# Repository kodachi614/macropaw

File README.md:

# MacroPaw Keypads

The MacroPaw keypads are a line of small yet fully-customizable mechanical
keyboards. (The name was originally from my son, years ago when he was young,
and the "paw" motif has kinda stuck.) The core of the MacroPaws is a Raspberry
Pi RP2040 with 16MiB of flash memory, a USB-C connector, and an attached key
matrix and RGB LEDs (which may or may not be under the keys). Some MacroPaws
have more capability than others; all are crazy customizable by writing Python
code. (Yes. Python. On a keyboard. It's insane and wonderful to live in the
future.)

|  |  |
| :-: | :-: |
| _Assembled KnGXT_     | _KnGXT PCB_ |

Currently extant MacroPaw boards include:

| Board ID | Description |
| :-: | :- |
| KnGXT | Mostly a proof-of-concept for an RP2040-based USB HID: it has 14 hotswappable MX keyswitches in a 3x5 layout like a number pad (including one 2U key, which is why it's 14 instead of 15), two rotary encoders with pushbuttons, and a bunch of RGB LEDs under the encoders and keys. |
| KnGYT | Mostly a proof-of-concept for double-sided assembly. It has ten hotswappable MX keyswitches in a 5x2 grid, ten RGB LEDs under the keys, and no rotary encoders. It's _much_ smaller than its sibling the KnGXT, because most of the electronics are on the back of the board. |
| Beatboxer KnH0F | A single-sided embedded keyboard controller for use in a [custom life-sized drum machine]. It has 8 RGB LEDs on the front of the board for hardware test and debugging, and its key matrix is an 8x8 grid that's mechanically arranged as a 16x4 grid of arcade buttons. |

[custom life-sized drum machine]: https://sig.gy/bbox/

Both the firmware and the hardware of the MacroPaws are **open source**.

## Firmware

The firmware is licensed under the GNU General Public License, version 3.0 or
later.

The `firmware` directory within each board's directory includes the firmware
source code firmware and the firmware license (in `firmware/LICENSE`).

The MacroPaw firmware is based on the [KMK Firmware], and on Adafruit's
[CircuitPython] and the [NeoPixelBackground] class. See
[BUILDING.md](BUILDING.md) for details about how to build the firmware,
including information about the versions of CircuitPython and KMK that are
used and how to get them.

Of course, if you don't want to build your own, you can just grab prebuilt
firmware for the [MacroPaw KnGXT], [MacroPaw KnGYT], and [MacroPaw Beatboxer
KnH0F] boards.

[KMK Firmware]: https://github.com/KMKfw/kmk_firmware/
[CircuitPython]: https://circuitpython.org/
[NeoPixelBackground]: https://learn.adafruit.com/intro-to-rp2040-pio-with-circuitpython/advanced-using-pio-to-drive-neopixels-in-the-background
[MacroPaw KnGXT]: https://www.kodachi.com/firmware/macropaw-KnGXT.uf2
[MacroPaw KnGYT]: https://www.kodachi.com/firmware/macropaw-KnGYT.uf2
[MacroPaw Beatboxer KnH0F]: https://www.kodachi.com/firmware/macropaw-Beatboxer.uf2

## Hardware

The hardware is licensed under the CERN Open Hardware License, version 2.0
or higher, Strongly Reciprocal.

The `hardware` directory within each board's directory includes the [KiCad] 7
design files for the hardware, the fabrication outputs used for the official
production runs of the hardware, and of course the hardware license (in
`hardware/LICENSE`).

[KiCad]: https://www.kicad.org/

## 3D Models

The `models` directory within some boards' directories includes the 3D models
for cases, etc., for the board. Boards without a `models` directory haven't
had models made yet!

The models are also licensed under the CERN Open Hardware License, version 2.0
or higher, Strongly Reciprocal.

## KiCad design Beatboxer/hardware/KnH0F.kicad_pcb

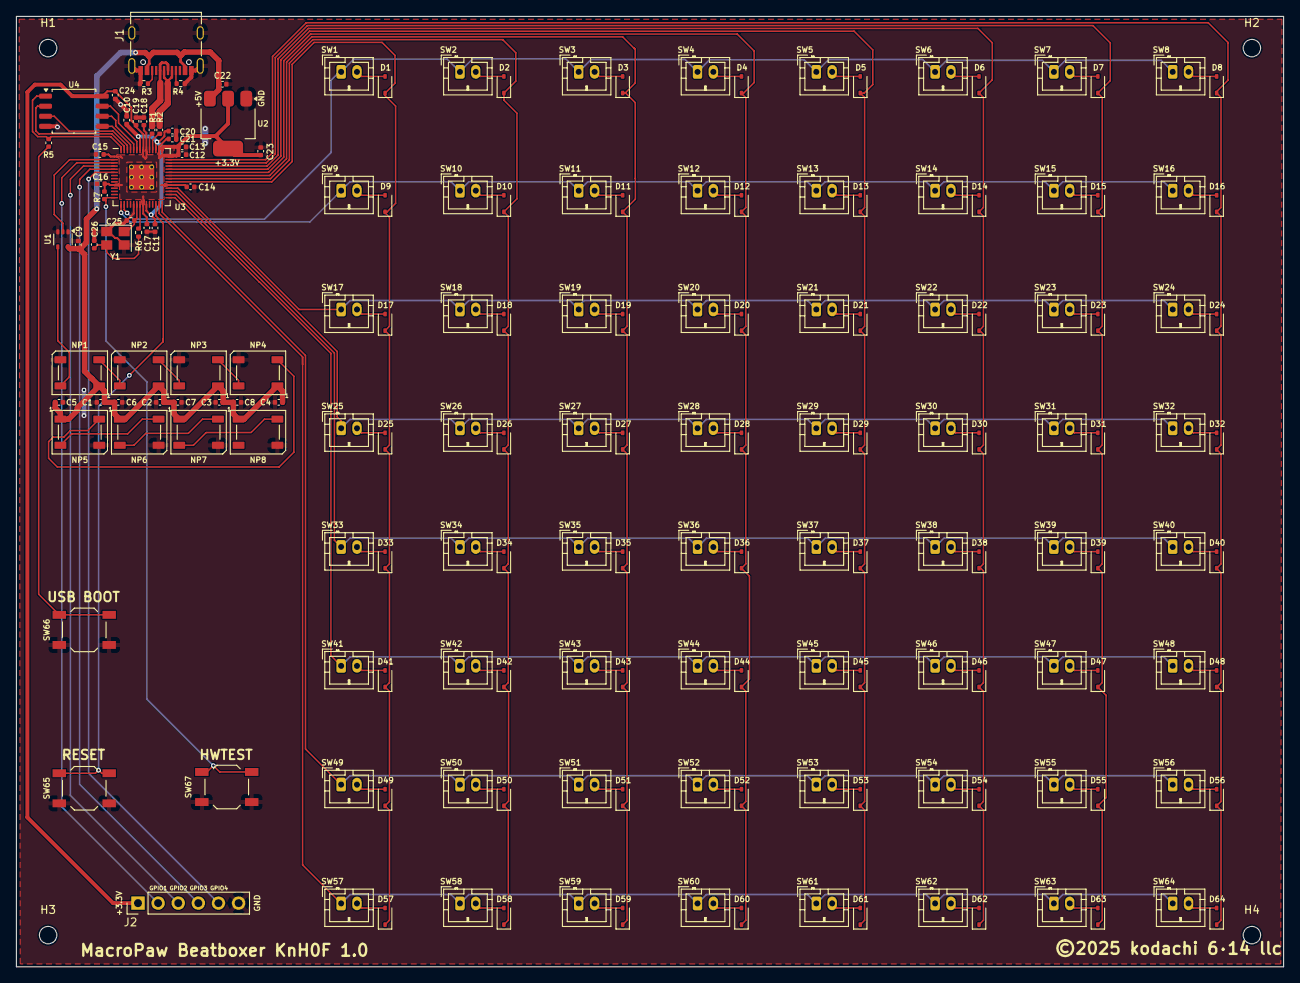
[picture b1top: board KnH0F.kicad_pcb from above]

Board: 2 copper layers, 160.0 x 120.0 mm, 183 parts (0 on the bottom side), 115 nets.

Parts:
C1, C2, C3, C4, C5, C6, C7, C8, C9, C22, C23, C24: 10uF; C_0402_1005Metric
C10, C11, C12, C13, C14, C15, C16, C17, C18, C19: 100nF; C_0402_1005Metric
C20, C21: 1uF; C_0402_1005Metric
C25, C26: 30pF; C_0402_1005Metric
D1, D2, D3, D4, D5, D6, D7, D8, D9, D10, D11, D12, D13, D14, D15, D16, D17, D18, D19, D20, D21, D22, D23, D24, D25, D26, D27, D28, D29, D30, D31, D32, D33, D34, D35, D36, D37, D38, D39, D40, D41, D42, D43, D44, D45, D46, D47, D48, D49, D50, D51, D52, D53, D54, D55, D56, D57, D58, D59, D60, D61, D62, D63, D64: 1N4148; D_SOD-323
H1, H2, H3, H4: MountingHole; MountingHole_2.2mm_M2
J1: USB_C_Receptacle_USB2.0_16P; USB_C_Receptacle_Palconn_UTC16-G
J2: Conn_01x06_Pin; PinHeader_1x06_P2.54mm_Vertical
NP1, NP2, NP3, NP4, NP5, NP6, NP7, NP8: WS2812B; LED_WS2812B_PLCC4_5.0x5.0mm_P3.2mm
R1, R2: 27; C_0402_1005Metric
R3, R4: 5.1k; R_0402_1005Metric
R5, R7: 1k; C_0402_1005Metric
R6: 1k; R_0402_1005Metric
SW1, SW2, SW3, SW4, SW5, SW6, SW7, SW8, SW9, SW10, SW11, SW12, SW13, SW14, SW15, SW16, SW17, SW18, SW19, SW20, SW21, SW22, SW23, SW24, SW25, SW26, SW27, SW28, SW29, SW30, SW31, SW32, SW33, SW34, SW35, SW36, SW37, SW38, SW39, SW40, SW41, SW42, SW43, SW44, SW45, SW46, SW47, SW48, SW49, SW50, SW51, SW52, SW53, SW54, SW55, SW56, SW57, SW58, SW59, SW60, SW61, SW62, SW63, SW64: SW_Push_45deg; JST_PH_B2B-PH-K_1x02_P2.00mm_Vertical
SW65, SW66, SW67: SW_Push; SW_SPST_TL3342
U1: 74AHC1G125; SOT-353_SC-70-5
U2: AMS1117-3.3; SOT-223-3_TabPin2
U3: RP2040; RP2040-QFN-56
U4: W25Q128JVS; SOIC-8_5.3x5.3mm_P1.27mm
Y1: 12MHz; Crystal_SMD_3225-4Pin_3.2x2.5mm

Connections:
+1V1: C10.1, C11.1, C20.1, U3.23 (DVDD), U3.45 (VREG_VOUT), U3.50 (DVDD)
+3V3: C12.1, C13.1, C14.1, C15.1, C16.1, C17.1, C18.1, C19.1, C21.1, C23.1, C24.1, J2.1, R7.1, U2.2 (VO), U3.1 (IOVDD), U3.10 (IOVDD), U3.22 (IOVDD), U3.33 (IOVDD), U3.42 (IOVDD), U3.43 (ADC_AVDD), U3.44 (VREG_IN), U3.48 (USB_VDD), U3.49 (IOVDD), U4.8 (VCC)
+5V: C1.1, C2.1, C3.1, C4.1, C5.1, C6.1, C7.1, C8.1, C9.1, C22.1, J1.A4 (VBUS), J1.A9 (VBUS), J1.B4 (VBUS), J1.B9 (VBUS), NP1.1 (VDD), NP2.1 (VDD), NP3.1 (VDD), NP4.1 (VDD), NP5.1 (VDD), NP6.1 (VDD), NP7.1 (VDD), NP8.1 (VDD), U1.5 (VCC), U2.3 (VI)
/GPIO1: J2.2, U3.3 (GPIO1)
/GPIO2: J2.3, U3.4 (GPIO2)
/GPIO3: J2.4, U3.5 (GPIO3)
/GPIO4: J2.5, U3.6 (GPIO4)
/HWTEST: R7.2, SW67.1, U3.14 (GPIO11)
/NEO3V3: U1.2, U3.2 (GPIO0)
/NEOPXL: NP1.4 (DIN), U1.4
/QSPI_SCLK: U3.52 (QSPI_SCLK), U4.6 (CLK)
/QSPI_SD0: U3.53 (QSPI_SD0), U4.5 (DI/IO_{0})
/QSPI_SD1: U3.55 (QSPI_SD1), U4.2 (DO/IO_{1})
/QSPI_SD2: U3.54 (QSPI_SD2), U4.3 (~WP/IO_{2})
/QSPI_SD3: U3.51 (QSPI_SD3), U4.7 (~HOLD/~RESET/IO_{3})
/QSPI_SS: R5.1, U3.56 (QSPI_SS), U4.1 (~CS)
/RUN: SW65.2, U3.26 (RUN)
/USB_CC1: J1.A5 (CC1), R4.2
/USB_CC2: J1.B5 (CC2), R3.2
/USB_D+: J1.A6 (D+), J1.B6 (D+), R1.1
/USB_D-: J1.A7 (D-), J1.B7 (D-), R2.1
/XIN: C25.1, U3.20 (XIN), Y1.1
/XOUT: R6.1, U3.21 (XOUT)
/~USB_BOOT: R5.2, SW66.2
COL0: D1.1 (K), D9.1 (K), D17.1 (K), D25.1 (K), D33.1 (K), D41.1 (K), D49.1 (K), D57.1 (K), U3.34 (GPIO22)
COL1: D2.1 (K), D10.1 (K), D18.1 (K), D26.1 (K), D34.1 (K), D42.1 (K), D50.1 (K), D58.1 (K), U3.35 (GPIO23)
COL2: D3.1 (K), D11.1 (K), D19.1 (K), D27.1 (K), D35.1 (K), D43.1 (K), D51.1 (K), D59.1 (K), U3.36 (GPIO24)
COL3: D4.1 (K), D12.1 (K), D20.1 (K), D28.1 (K), D36.1 (K), D44.1 (K), D52.1 (K), D60.1 (K), U3.37 (GPIO25)
COL4: D5.1 (K), D13.1 (K), D21.1 (K), D29.1 (K), D37.1 (K), D45.1 (K), D53.1 (K), D61.1 (K), U3.38 (GPIO26_ADC0)
COL5: D6.1 (K), D14.1 (K), D22.1 (K), D30.1 (K), D38.1 (K), D46.1 (K), D54.1 (K), D62.1 (K), U3.39 (GPIO27_ADC1)
COL6: D7.1 (K), D15.1 (K), D23.1 (K), D31.1 (K), D39.1 (K), D47.1 (K), D55.1 (K), D63.1 (K), U3.40 (GPIO28_ADC2)
COL7: D8.1 (K), D16.1 (K), D24.1 (K), D32.1 (K), D40.1 (K), D48.1 (K), D56.1 (K), D64.1 (K), U3.41 (GPIO29_ADC3)
GND: C1.2, C2.2, C3.2, C4.2, C5.2, C6.2, C7.2, C8.2, C9.2, C10.2, C11.2, C12.2, C13.2, C14.2, C15.2, C16.2, C17.2, C18.2, C19.2, C20.2, C21.2, C22.2, C23.2, C24.2, C25.2, C26.2, J1.A1 (GND), J1.A12 (GND), J1.B1 (GND), J1.B12 (GND), J1.S1 (SHIELD), J2.6, NP1.3 (VSS), NP2.3 (VSS), NP3.3 (VSS), NP4.3 (VSS), NP5.3 (VSS), NP6.3 (VSS), NP7.3 (VSS), NP8.3 (VSS), R3.1, R4.1, SW65.1, SW66.1, SW67.2, U1.1, U1.3 (GND), U2.1 (GND), U3.19 (TESTEN), U3.57 (GND), U4.4 (GND), Y1.2, Y1.4
unnamed: C26.1, R6.2, Y1.3
unnamed: D1.2 (A), SW1.2
unnamed: D2.2 (A), SW2.2
unnamed: D3.2 (A), SW3.2
unnamed: D4.2 (A), SW4.2
unnamed: D5.2 (A), SW5.2
unnamed: D6.2 (A), SW6.2
unnamed: D7.2 (A), SW7.2
unnamed: D8.2 (A), SW8.2
unnamed: D9.2 (A), SW9.2
unnamed: D10.2 (A), SW10.2
unnamed: D11.2 (A), SW11.2
unnamed: D12.2 (A), SW12.2
unnamed: D13.2 (A), SW13.2
unnamed: D14.2 (A), SW14.2
unnamed: D15.2 (A), SW15.2
unnamed: D16.2 (A), SW16.2
unnamed: D17.2 (A), SW17.2
unnamed: D18.2 (A), SW18.2
unnamed: D19.2 (A), SW19.2
unnamed: D20.2 (A), SW20.2
unnamed: D21.2 (A), SW21.2
unnamed: D22.2 (A), SW22.2
unnamed: D23.2 (A), SW23.2
unnamed: D24.2 (A), SW24.2
unnamed: D25.2 (A), SW25.2
unnamed: D26.2 (A), SW26.2
unnamed: D27.2 (A), SW27.2
unnamed: D28.2 (A), SW28.2
unnamed: D29.2 (A), SW29.2
unnamed: D30.2 (A), SW30.2
unnamed: D31.2 (A), SW31.2
unnamed: D32.2 (A), SW32.2
unnamed: D33.2 (A), SW33.2
unnamed: D34.2 (A), SW34.2
unnamed: D35.2 (A), SW35.2
unnamed: D36.2 (A), SW36.2
unnamed: D37.2 (A), SW37.2
unnamed: D38.2 (A), SW38.2
unnamed: D39.2 (A), SW39.2
unnamed: D40.2 (A), SW40.2
unnamed: D41.2 (A), SW41.2
unnamed: D42.2 (A), SW42.2
unnamed: D43.2 (A), SW43.2
unnamed: D44.2 (A), SW44.2
unnamed: D45.2 (A), SW45.2
unnamed: D46.2 (A), SW46.2
unnamed: D47.2 (A), SW47.2
unnamed: D48.2 (A), SW48.2
unnamed: D49.2 (A), SW49.2
unnamed: D50.2 (A), SW50.2
unnamed: D51.2 (A), SW51.2
unnamed: D52.2 (A), SW52.2
unnamed: D53.2 (A), SW53.2
unnamed: D54.2 (A), SW54.2
unnamed: D55.2 (A), SW55.2
unnamed: D56.2 (A), SW56.2
unnamed: D57.2 (A), SW57.2
unnamed: D58.2 (A), SW58.2
unnamed: D59.2 (A), SW59.2
unnamed: D60.2 (A), SW60.2
unnamed: D61.2 (A), SW61.2
unnamed: D62.2 (A), SW62.2
unnamed: D63.2 (A), SW63.2
unnamed: D64.2 (A), SW64.2
unnamed: NP1.2 (DOUT), NP2.4 (DIN)
unnamed: NP2.2 (DOUT), NP3.4 (DIN)
unnamed: NP3.2 (DOUT), NP4.4 (DIN)
unnamed: NP4.2 (DOUT), NP5.4 (DIN)
unnamed: NP5.2 (DOUT), NP6.4 (DIN)
unnamed: NP6.2 (DOUT), NP7.4 (DIN)
unnamed: NP7.2 (DOUT), NP8.4 (DIN)
unnamed: R2.2, U3.46 (USB_DM)
unnamed: R1.2, U3.47 (USB_DP)
ROW0: SW1.1, SW2.1, SW3.1, SW4.1, SW5.1, SW6.1, SW7.1, SW8.1, U3.16 (GPIO13)
ROW1: SW9.1, SW10.1, SW11.1, SW12.1, SW13.1, SW14.1, SW15.1, SW16.1, U3.15 (GPIO12)
ROW2: SW17.1, SW18.1, SW19.1, SW20.1, SW21.1, SW22.1, SW23.1, SW24.1, U3.32 (GPIO21)
ROW3: SW25.1, SW26.1, SW27.1, SW28.1, SW29.1, SW30.1, SW31.1, SW32.1, U3.31 (GPIO20)
ROW4: SW33.1, SW34.1, SW35.1, SW36.1, SW37.1, SW38.1, SW39.1, SW40.1, U3.30 (GPIO19)
ROW5: SW41.1, SW42.1, SW43.1, SW44.1, SW45.1, SW46.1, SW47.1, SW48.1, U3.29 (GPIO18)
ROW6: SW49.1, SW50.1, SW51.1, SW52.1, SW53.1, SW54.1, SW55.1, SW56.1, U3.28 (GPIO17)
ROW7: SW57.1, SW58.1, SW59.1, SW60.1, SW61.1, SW62.1, SW63.1, SW64.1, U3.27 (GPIO16)

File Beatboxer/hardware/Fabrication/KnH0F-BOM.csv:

Comment,Designator,Footprint,LCSC Part Number
10uF,"C1,C2,C3,C4,C5,C6,C7,C8,C9,C22,C23,C24",0402,C15525
100nF,"C10,C11,C12,C13,C14,C15,C16,C17,C18,C19",0402,C1525
1uF,"C20,C21",0402,C52923
30pF,"C25,C26",0402,C1570
1N4148,"D1,D2,D3,D4,D5,D6,D7,D8,D9,D10,D11,D12,D13,D14,D15,D16,D17,D18,D19,D20,D21,D22,D23,D24,D25,D26,D27,D28,D29,D30,D31,D32,D33,D34,D35,D36,D37,D38,D39,D40,D41,D42,D43,D44,D45,D46,D47,D48,D49,D50,D51,D52,D53,D54,D55,D56,D57,D58,D59,D60,D61,D62,D63,D64",SOD-323,C2128
USB_C_Receptacle_USB2.0_16P,J1,USB_C_Receptacle_Palconn_UTC16-G,C165948
WS2812B,"NP1,NP2,NP3,NP4,NP5,NP6,NP7,NP8",PLCC4 5.0x5.0mm,C2761795
27,"R1,R2",0402,C25100
5.1k,"R3,R4",0402,C25905
1k,"R5,R7",0402,C11702
1k,R6,0402,C11702
SW_Push_45deg,"SW1,SW2,SW3,SW4,SW5,SW6,SW7,SW8,SW9,SW10,SW11,SW12,SW13,SW14,SW15,SW16,SW17,SW18,SW19,SW20,SW21,SW22,SW23,SW24,SW25,SW26,SW27,SW28,SW29,SW30,SW31,SW32,SW33,SW34,SW35,SW36,SW37,SW38,SW39,SW40,SW41,SW42,SW43,SW44,SW45,SW46,SW47,SW48,SW49,SW50,SW51,SW52,SW53,SW54,SW55,SW56,SW57,SW58,SW59,SW60,SW61,SW62,SW63,SW64",JST PH B2B-PH-K 1x02 P2.00mm Vertical,C131337
SW_Push,"SW65,SW66,SW67",SPST_TL3342,C318884
74AHC1G125,U1,SOT-353,C151417
AMS1117-3.3,U2,SOT-223,C6186
RP2040,U3,QFN-56,C2040
W25Q128JVS,U4,SOIC-8 5.3x5.3mm P1.27mm,C97521
12MHz,Y1,SMD_3225,C9002

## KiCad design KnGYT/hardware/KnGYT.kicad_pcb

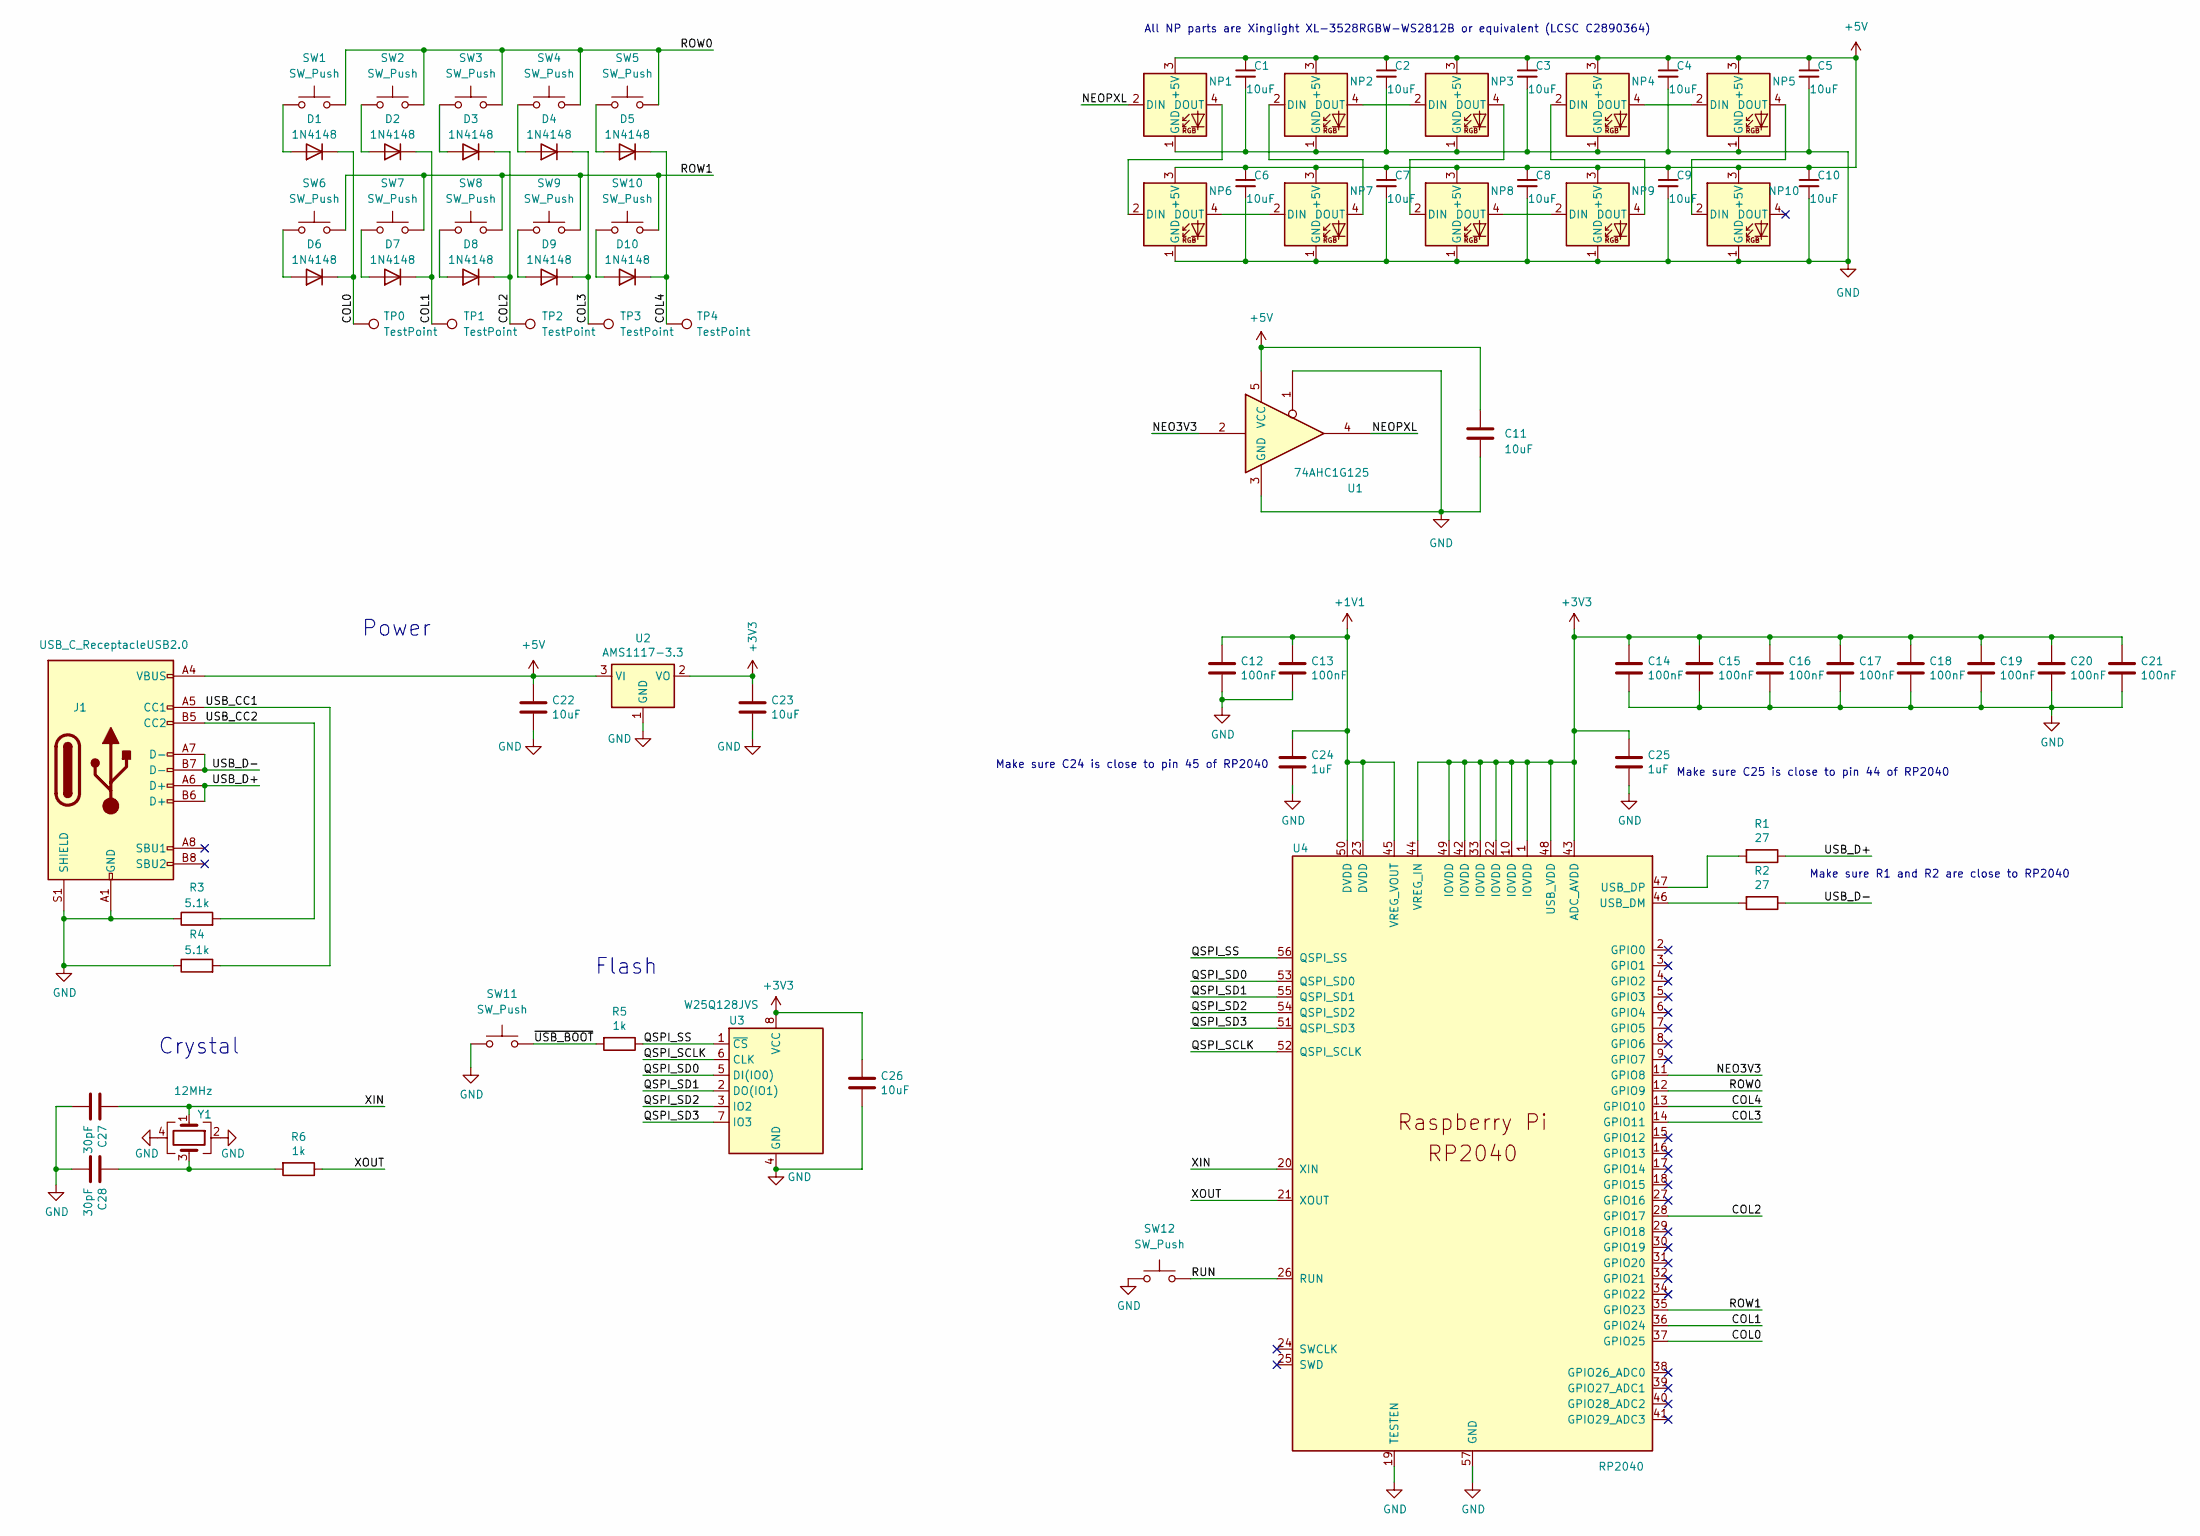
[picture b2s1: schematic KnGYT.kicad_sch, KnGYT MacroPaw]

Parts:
C1, C2, C3, C4, C5, C6, C7, C8, C9, C10, C11, C22, C23, C26: 10uF; C_0402_1005Metric; LCSC C15525
C12, C13, C14, C15, C16, C17, C18, C19, C20, C21: 100nF; C_0402_1005Metric; LCSC C1525
C24, C25: 1uF; C_0402_1005Metric; LCSC C52923
C27, C28: 30pF; C_0402_1005Metric; LCSC C1570
D1, D2, D3, D4, D5, D6, D7, D8, D9, D10: 1N4148; D_SOD-323F; LCSC C2128
J1: USB_C_ReceptacleUSB2.0; USB_C_Receptacle_Palconn_UTC16-G; LCSC C165948
NP1, NP2, NP3, NP4, NP5, NP6, NP7, NP8, NP9, NP10: WS2812B; LED XL-3528RGBW-WS2812B (3.5x2.8, C2890364); LCSC C2890364
R1, R2: 27; C_0402_1005Metric; LCSC C25100
R3, R4: 5.1k; R_0402_1005Metric; LCSC C25905
R5: 1k; C_0402_1005Metric; LCSC C11702
R6: 1k; R_0402_1005Metric; LCSC C11702
SW1, SW2, SW3, SW4, SW5, SW6, SW7, SW8, SW9, SW10: SW_Push; Flipped_Hotswap_Kailh_MX_1.00u (C5184526); LCSC C5184526
SW11, SW12: SW_Push; SW_SPST_TL3342; LCSC C318884
TP0, TP1, TP2, TP3, TP4: TestPoint; TestPoint_Pad_1.5x1.5mm
U1: 74AHC1G125; SOT-353_SC-70-5; LCSC C151417
U2: AMS1117-3.3; SOT-223-3_TabPin2; LCSC C6186
U3: W25Q128JVS; SOIC-8_5.23x5.23mm_P1.27mm; LCSC C97521
U4: RP2040; RP2040-QFN-56; LCSC C2040
Y1: 12MHz; Crystal_SMD_3225-4Pin_3.2x2.5mm; LCSC C9002

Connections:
+1V1: C12.1, C13.1, C24.1, U4.23 (DVDD), U4.45 (VREG_VOUT), U4.50 (DVDD)
+3V3: C14.1, C15.1, C16.1, C17.1, C18.1, C19.1, C20.1, C21.1, C23.1, C25.1, C26.1, U2.2 (VO), U3.8 (VCC), U4.1 (IOVDD), U4.10 (IOVDD), U4.22 (IOVDD), U4.33 (IOVDD), U4.42 (IOVDD), U4.43 (ADC_AVDD), U4.44 (VREG_IN), U4.48 (USB_VDD), U4.49 (IOVDD)
+5V: C1.1, C2.1, C3.1, C4.1, C5.1, C6.1, C7.1, C8.1, C9.1, C10.1, C11.1, C22.1, J1.A4 (VBUS), J1.A9 (VBUS), J1.B4 (VBUS), J1.B9 (VBUS), NP1.3 (+5V), NP2.3 (+5V), NP3.3 (+5V), NP4.3 (+5V), NP5.3 (+5V), NP6.3 (+5V), NP7.3 (+5V), NP8.3 (+5V), NP9.3 (+5V), NP10.3 (+5V), U1.5 (VCC), U2.3 (VI)
/COL0: D1.1 (K), D6.1 (K), TP0.1, U4.37 (GPIO25)
/COL1: D2.1 (K), D7.1 (K), TP1.1, U4.36 (GPIO24)
/COL2: D3.1 (K), D8.1 (K), TP2.1, U4.28 (GPIO17)
/COL3: D4.1 (K), D9.1 (K), TP3.1, U4.14 (GPIO11)
/COL4: D5.1 (K), D10.1 (K), TP4.1, U4.13 (GPIO10)
/NEO3V3: U1.2, U4.11 (GPIO8)
/NEOPXL: NP1.2 (DIN), U1.4
/QSPI_SCLK: U3.6 (CLK), U4.52 (QSPI_SCLK)
/QSPI_SD0: U3.5 (DI(IO0)), U4.53 (QSPI_SD0)
/QSPI_SD1: U3.2 (DO(IO1)), U4.55 (QSPI_SD1)
/QSPI_SD2: U3.3 (IO2), U4.54 (QSPI_SD2)
/QSPI_SD3: U3.7 (IO3), U4.51 (QSPI_SD3)
/QSPI_SS: R5.1, U3.1 (~CS), U4.56 (QSPI_SS)
/ROW0: SW1.2, SW2.2, SW3.2, SW4.2, SW5.2, U4.12 (GPIO9)
/ROW1: SW6.2, SW7.2, SW8.2, SW9.2, SW10.2, U4.35 (GPIO23)
/RUN: SW12.2, U4.26 (RUN)
/USB_CC1: J1.A5 (CC1), R4.2
/USB_CC2: J1.B5 (CC2), R3.2
/USB_D+: J1.A6 (D+), J1.B6 (D+), R1.1
/USB_D-: J1.A7 (D-), J1.B7 (D-), R2.1
/XIN: C27.1, U4.20 (XIN), Y1.1
/XOUT: R6.1, U4.21 (XOUT)
/~USB_BOOT: R5.2, SW11.2
GND: C1.2, C2.2, C3.2, C4.2, C5.2, C6.2, C7.2, C8.2, C9.2, C10.2, C11.2, C12.2, C13.2, C14.2, C15.2, C16.2, C17.2, C18.2, C19.2, C20.2, C21.2, C22.2, C23.2, C24.2, C25.2, C26.2, C27.2, C28.2, J1.A1 (GND), J1.A12 (GND), J1.B1 (GND), J1.B12 (GND), J1.S1 (SHIELD), NP1.1 (GND), NP2.1 (GND), NP3.1 (GND), NP4.1 (GND), NP5.1 (GND), NP6.1 (GND), NP7.1 (GND), NP8.1 (GND), NP9.1 (GND), NP10.1 (GND), R3.1, R4.1, SW11.1, SW12.1, U1.1, U1.3 (GND), U2.1 (GND), U3.4 (GND), U4.19 (TESTEN), U4.57 (GND), Y1.2, Y1.4
unnamed: C28.1, R6.2, Y1.3
unnamed: D1.2 (A), SW1.1
unnamed: D2.2 (A), SW2.1
unnamed: D3.2 (A), SW3.1
unnamed: D4.2 (A), SW4.1
unnamed: D5.2 (A), SW5.1
unnamed: D6.2 (A), SW6.1
unnamed: D7.2 (A), SW7.1
unnamed: D8.2 (A), SW8.1
unnamed: D9.2 (A), SW9.1
unnamed: D10.2 (A), SW10.1
unnamed: NP1.4 (DOUT), NP6.2 (DIN)
unnamed: NP2.2 (DIN), NP7.4 (DOUT)
unnamed: NP2.4 (DOUT), NP3.2 (DIN)
unnamed: NP3.4 (DOUT), NP8.2 (DIN)
unnamed: NP4.2 (DIN), NP9.4 (DOUT)
unnamed: NP4.4 (DOUT), NP5.2 (DIN)
unnamed: NP6.4 (DOUT), NP7.2 (DIN)
unnamed: NP8.4 (DOUT), NP9.2 (DIN)
unnamed: NP5.4 (DOUT), NP10.2 (DIN)
unnamed: R2.2, U4.46 (USB_DM)
unnamed: R1.2, U4.47 (USB_DP)

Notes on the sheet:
Crystal
Make sure R1 and R2 are close to RP2040
Make sure C25 is close to pin 44 of RP2040
All NP parts are Xinglight XL-3528RGBW-WS2812B or equivalent (LCSC C2890364)
Make sure C24 is close to pin 45 of RP2040
Flash
Power

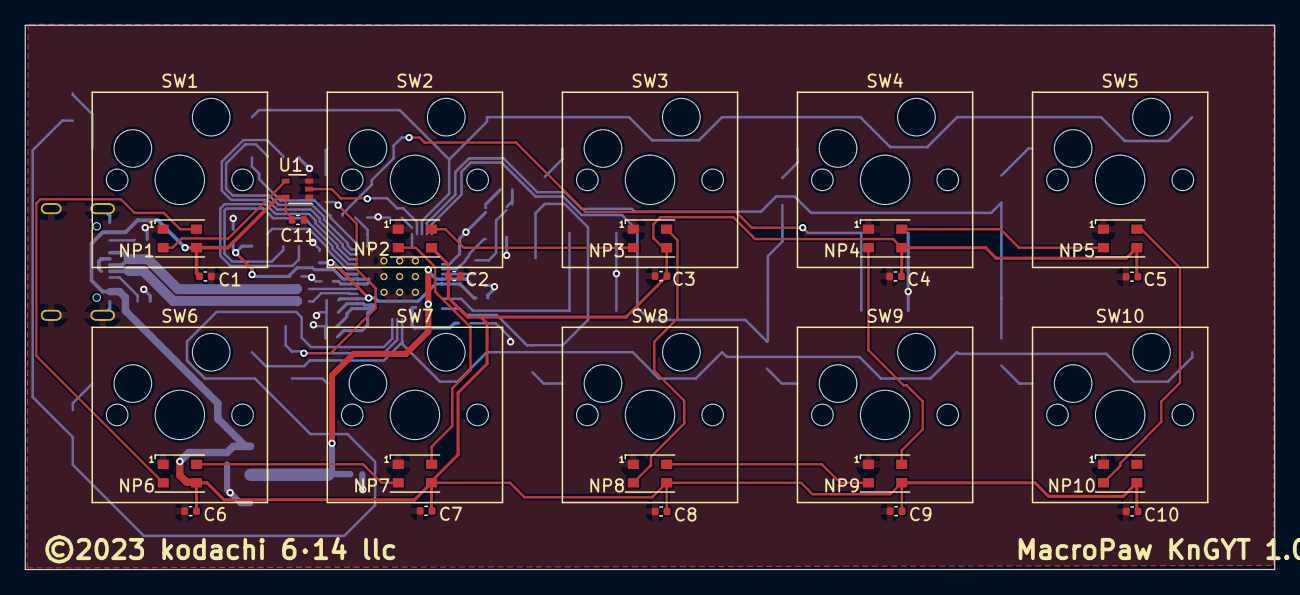
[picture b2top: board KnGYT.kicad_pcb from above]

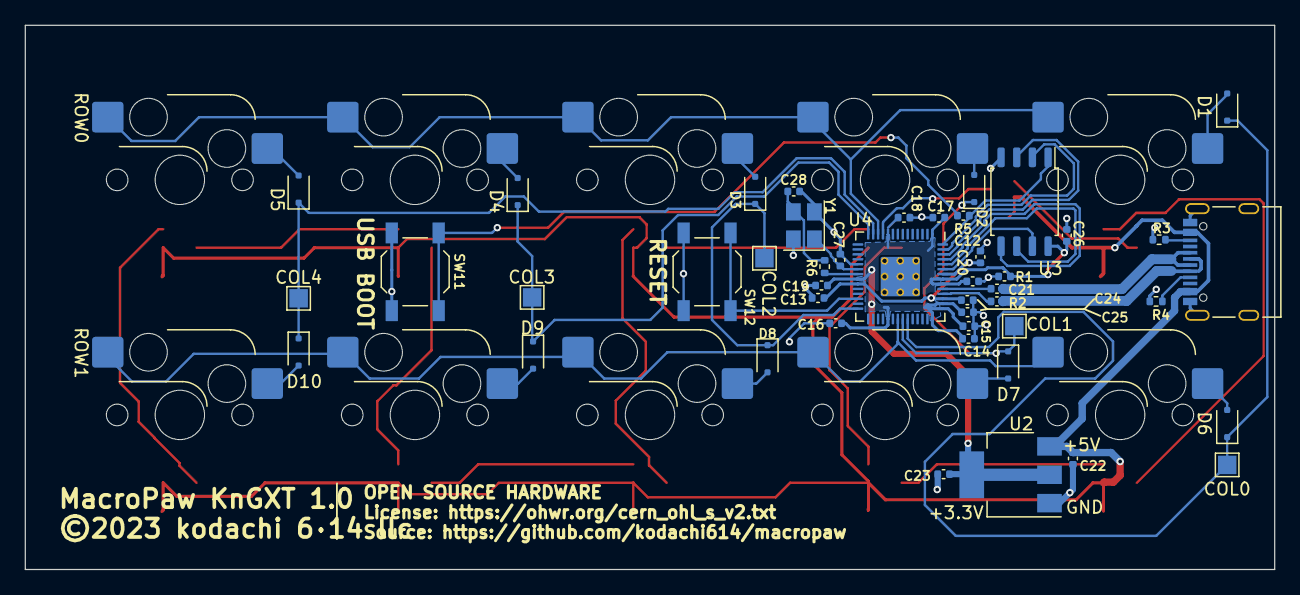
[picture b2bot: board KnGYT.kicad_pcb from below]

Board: 2 copper layers, 101.2 x 44.1 mm, 77 parts (55 on the bottom side), 49 nets.

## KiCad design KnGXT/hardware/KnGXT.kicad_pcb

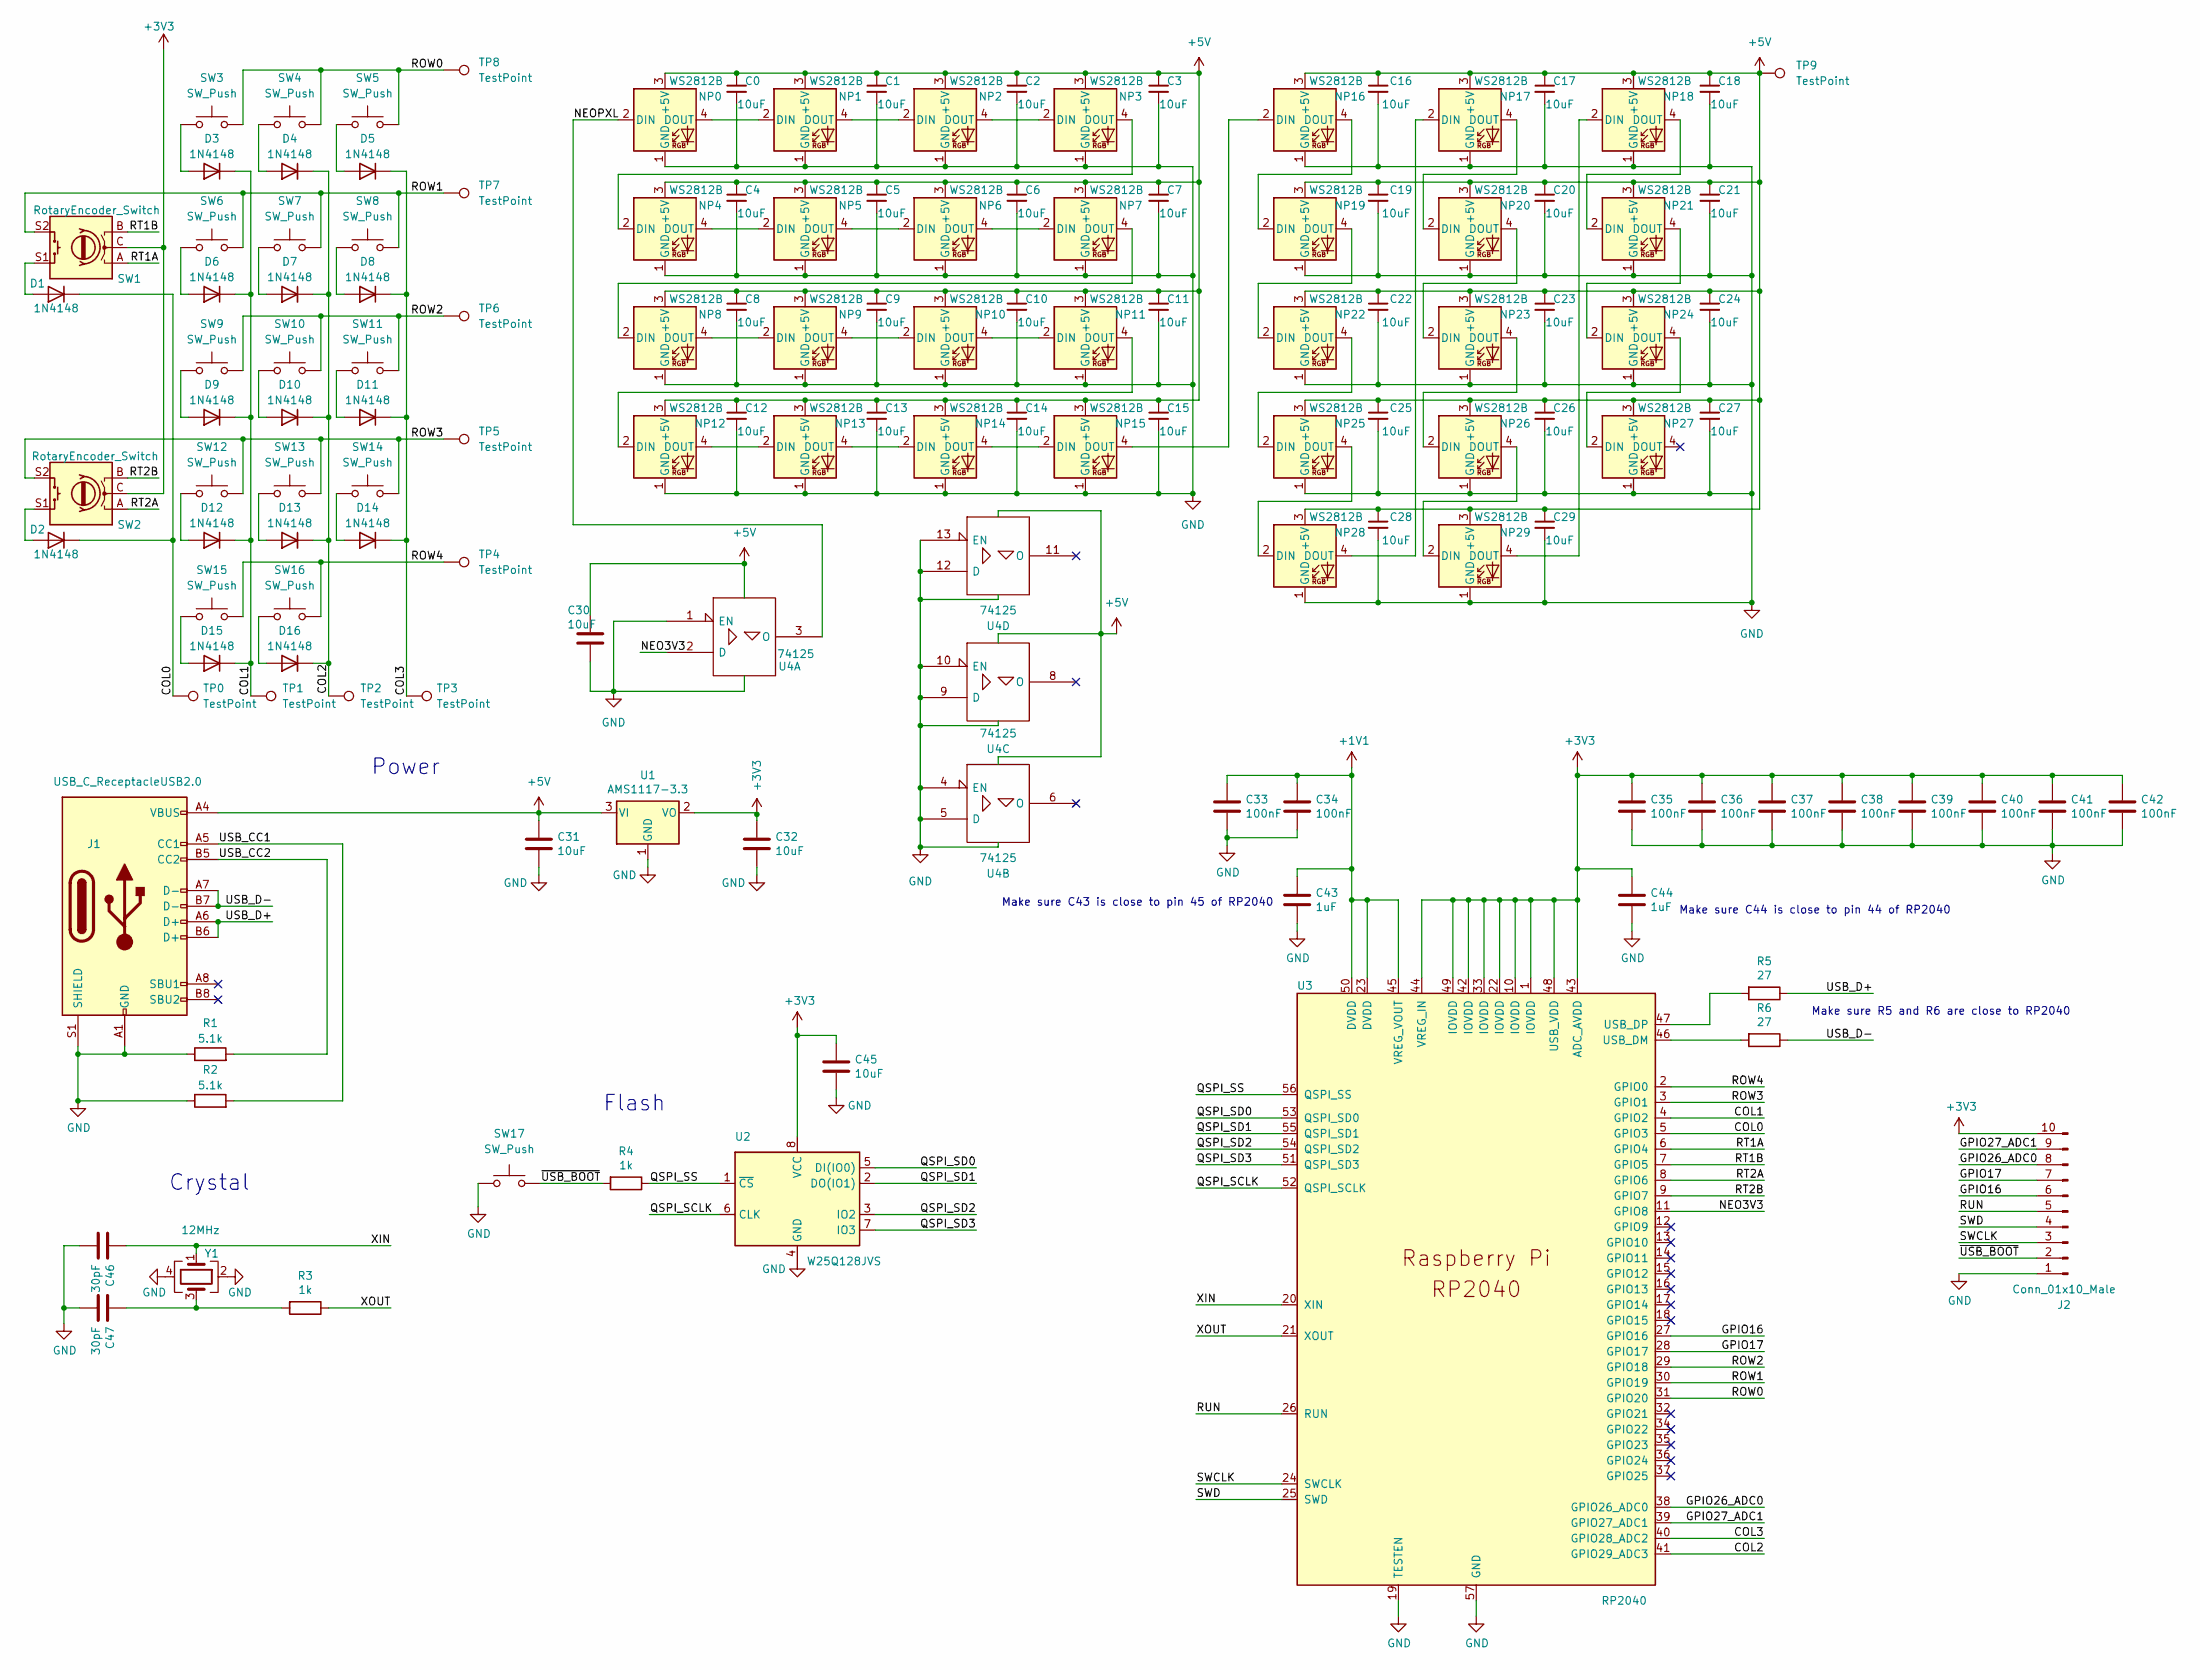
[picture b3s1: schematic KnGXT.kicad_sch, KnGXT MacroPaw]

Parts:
C0, C1, C2, C3, C4, C5, C6, C7, C8, C9, C10, C11, C12, C13, C14, C15, C16, C17, C18, C19, C20, C21, C22, C23, C24, C25, C26, C27, C28, C29, C30, C31, C32, C45: 10uF; C_0402_1005Metric; LCSC C15525
C33, C34, C35, C36, C37, C38, C39, C40, C41, C42: 100nF; C_0402_1005Metric; LCSC C1525
C43, C44: 1uF; C_0402_1005Metric; LCSC C52923
C46, C47: 30pF; C_0402_1005Metric; LCSC C1570
D1, D2, D3, D4, D5, D6, D7, D8, D9, D10, D11, D12, D13, D14, D15, D16: 1N4148; D_SOD-323F; LCSC C2128
J1: USB_C_ReceptacleUSB2.0; USB_C_Receptacle_Palconn_UTC16-G; LCSC C165948
J2: Conn_01x10_Male; PinHeader_1x10_P2.54mm_Horizontal
NP0, NP1, NP2, NP3, NP4, NP5, NP6, NP7, NP8, NP9, NP10, NP11, NP12, NP13, NP14, NP15, NP16, NP17, NP18, NP19, NP20, NP21, NP22, NP23, NP24, NP25, NP26, NP27, NP28, NP29: WS2812B; LED XL-3528RGBW-WS2812B (3.5x2.8, C2890364); LCSC C2890364
R1, R2: 5.1k; R_0402_1005Metric; LCSC C25905
R3: 1k; R_0402_1005Metric; LCSC C11702
R4: 1k; C_0402_1005Metric; LCSC C11702
R5, R6: 27; C_0402_1005Metric; LCSC C25100
SW1, SW2: RotaryEncoder_Switch; RotaryEncoder_Alps_EC12E-Switch_Vertical_H20mm
SW3, SW4, SW5, SW6, SW7, SW8, SW9, SW10, SW11, SW12, SW13, SW14, SW15: SW_Push; SW_Hotswap_Kailh_MX_1.00u
SW16: SW_Push; SW_Hotswap_Kailh_MX_2.00u
SW17: SW_Push; SW_SPST_TL3342; LCSC C318884
TP0, TP1, TP2, TP3, TP4, TP5, TP6, TP7, TP8, TP9: TestPoint; TestPoint_Loop_D1.80mm_Drill1.0mm_Beaded
U1: AMS1117-3.3; SOT-223-3_TabPin2; LCSC C6186
U2: W25Q128JVS; SOIC-8_5.23x5.23mm_P1.27mm; LCSC C97521
U3: RP2040; RP2040-QFN-56; LCSC C2040
U4: 74125; TSSOP-14_4.4x5mm_P0.65mm; LCSC C36365
Y1: 12MHz; Crystal_SMD_3225-4Pin_3.2x2.5mm; LCSC C9002

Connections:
+1V1: C33.1, C34.1, C43.1, U3.23 (DVDD), U3.45 (VREG_VOUT), U3.50 (DVDD)
+3V3: C32.1, C35.1, C36.1, C37.1, C38.1, C39.1, C40.1, C41.1, C42.1, C44.1, C45.1, J2.10, SW1.C, SW2.C, U1.2 (VO), U2.8 (VCC), U3.1 (IOVDD), U3.10 (IOVDD), U3.22 (IOVDD), U3.33 (IOVDD), U3.42 (IOVDD), U3.43 (ADC_AVDD), U3.44 (VREG_IN), U3.48 (USB_VDD), U3.49 (IOVDD)
+5V: C0.1, C1.1, C2.1, C3.1, C4.1, C5.1, C6.1, C7.1, C8.1, C9.1, C10.1, C11.1, C12.1, C13.1, C14.1, C15.1, C16.1, C17.1, C18.1, C19.1, C20.1, C21.1, C22.1, C23.1, C24.1, C25.1, C26.1, C27.1, C28.1, C29.1, C30.1, C31.1, J1.A4 (VBUS), J1.A9 (VBUS), J1.B4 (VBUS), J1.B9 (VBUS), NP0.3 (VDD), NP1.3 (+5V), NP2.3 (VDD), NP3.3 (VDD), NP4.3 (VDD), NP5.3 (VDD), NP6.3 (VDD), NP7.3 (VDD), NP8.3 (VDD), NP9.3 (VDD), NP10.3 (VDD), NP11.3 (VDD), NP12.3 (VDD), NP13.3 (VDD), NP14.3 (VDD), NP15.3 (VDD), NP16.3 (VDD), NP17.3 (VDD), NP18.3 (VDD), NP19.3 (VDD), NP20.3 (VDD), NP21.3 (VDD), NP22.3 (VDD), NP23.3 (VDD), NP24.3 (VDD), NP25.3 (VDD), NP26.3 (VDD), NP27.3 (VDD), NP28.3 (VDD), NP29.3 (VDD), TP9.1, U1.3 (VI), U4.14 (VCC); also elsewhere on the board
/COL0: D1.1 (K), D2.1 (K), TP0.1, U3.5 (GPIO3)
/COL1: D3.1 (K), D6.1 (K), D9.1 (K), D12.1 (K), D15.1 (K), TP1.1, U3.4 (GPIO2)
/COL2: D4.1 (K), D7.1 (K), D10.1 (K), D13.1 (K), D16.1 (K), TP2.1, U3.41 (GPIO29_ADC3)
/COL3: D5.1 (K), D8.1 (K), D11.1 (K), D14.1 (K), TP3.1, U3.40 (GPIO28_ADC2)
/GPIO16: J2.6, U3.27 (GPIO16)
/GPIO17: J2.7, U3.28 (GPIO17)
/GPIO26_ADC0: J2.8, U3.38 (GPIO26_ADC0)
/GPIO27_ADC1: J2.9, U3.39 (GPIO27_ADC1)
/NEO3V3: U3.11 (GPIO8), U4.2 (D)
/NEOPXL: NP0.2 (DIN), U4.3 (O)
/QSPI_SCLK: U2.6 (CLK), U3.52 (QSPI_SCLK)
/QSPI_SD0: U2.5 (DI(IO0)), U3.53 (QSPI_SD0)
/QSPI_SD1: U2.2 (DO(IO1)), U3.55 (QSPI_SD1)
/QSPI_SD2: U2.3 (IO2), U3.54 (QSPI_SD2)
/QSPI_SD3: U2.7 (IO3), U3.51 (QSPI_SD3)
/QSPI_SS: R4.1, U2.1 (~CS), U3.56 (QSPI_SS)
/ROW0: SW3.2, SW4.2, SW5.2, TP8.1, U3.31 (GPIO20)
/ROW1: SW1.S2, SW6.2, SW7.2, SW8.2, TP7.1, U3.30 (GPIO19)
/ROW2: SW9.2, SW10.2, SW11.2, TP6.1, U3.29 (GPIO18)
/ROW3: SW2.S2, SW12.2, SW13.2, SW14.2, TP5.1, U3.3 (GPIO1)
/ROW4: SW15.2, SW16.2, TP4.1, U3.2 (GPIO0)
/RT1A: SW1.A, U3.6 (GPIO4)
/RT1B: SW1.B, U3.7 (GPIO5)
/RT2A: SW2.A, U3.8 (GPIO6)
/RT2B: SW2.B, U3.9 (GPIO7)
/RUN: J2.5, U3.26 (RUN)
/SWCLK: J2.3, U3.24 (SWCLK)
/SWD: J2.4, U3.25 (SWD)
/USB_CC1: J1.A5 (CC1), R2.2
/USB_CC2: J1.B5 (CC2), R1.2
/USB_D+: J1.A6 (D+), J1.B6 (D+), R5.1
/USB_D-: J1.A7 (D-), J1.B7 (D-), R6.1
/XIN: C46.1, U3.20 (XIN), Y1.1
/XOUT: R3.1, U3.21 (XOUT)
/~USB_BOOT: J2.2, R4.2, SW17.2
GND: C0.2, C1.2, C2.2, C3.2, C4.2, C5.2, C6.2, C7.2, C8.2, C9.2, C10.2, C11.2, C12.2, C13.2, C14.2, C15.2, C16.2, C17.2, C18.2, C19.2, C20.2, C21.2, C22.2, C23.2, C24.2, C25.2, C26.2, C27.2, C28.2, C29.2, C30.2, C31.2, C32.2, C33.2, C34.2, C35.2, C36.2, C37.2, C38.2, C39.2, C40.2, C41.2, C42.2, C43.2, C44.2, C45.2, C46.2, C47.2, J1.A1 (GND), J1.A12 (GND), J1.B1 (GND), J1.B12 (GND), J1.S1 (SHIELD), J2.1, NP0.1 (VSS), NP1.1 (GND), NP2.1 (VSS), NP3.1 (VSS), NP4.1 (VSS), NP5.1 (VSS), NP6.1 (VSS), NP7.1 (VSS), NP8.1 (VSS), NP9.1 (VSS), NP10.1 (VSS), NP11.1 (VSS), NP12.1 (VSS), NP13.1 (VSS), NP14.1 (VSS), NP15.1 (VSS), NP16.1 (VSS), NP17.1 (VSS), NP18.1 (VSS), NP19.1 (VSS), NP20.1 (VSS), NP21.1 (VSS), NP22.1 (VSS), NP23.1 (VSS), NP24.1 (VSS), NP25.1 (VSS), NP26.1 (VSS), NP27.1 (VSS), NP28.1 (VSS), NP29.1 (VSS), R1.1, R2.1, SW17.1, U1.1 (GND), U2.4 (GND), U3.19 (TESTEN), U3.57 (GND), U4.1 (EN), U4.4 (EN), U4.5 (D), U4.7 (GND), U4.9 (D), U4.10 (EN), U4.12 (D), U4.13 (EN), Y1.2, Y1.4; also elsewhere on the board
unnamed: C47.1, R3.2, Y1.3
unnamed: D1.2 (A), SW1.S1
unnamed: D2.2 (A), SW2.S1
unnamed: D3.2 (A), SW3.1
unnamed: D4.2 (A), SW4.1
unnamed: D5.2 (A), SW5.1
unnamed: D6.2 (A), SW6.1
unnamed: D7.2 (A), SW7.1
unnamed: D8.2 (A), SW8.1
unnamed: D9.2 (A), SW9.1
unnamed: D10.2 (A), SW10.1
unnamed: D11.2 (A), SW11.1
unnamed: D12.2 (A), SW12.1
unnamed: D13.2 (A), SW13.1
unnamed: D14.2 (A), SW14.1
unnamed: D15.2 (A), SW15.1
unnamed: D16.2 (A), SW16.1
unnamed 56: NP0.4 (DOUT), NP1.2 (DIN); also elsewhere on the board
unnamed 57: NP1.4 (DOUT), NP2.2 (DIN); also elsewhere on the board
unnamed: NP2.4 (DOUT), NP3.2 (DIN)
unnamed: NP3.4 (DOUT), NP4.2 (DIN)
unnamed: NP4.4 (DOUT), NP5.2 (DIN)
unnamed: NP5.4 (DOUT), NP6.2 (DIN)
unnamed: NP6.4 (DOUT), NP7.2 (DIN)
unnamed: NP7.4 (DOUT), NP8.2 (DIN)
unnamed: NP8.4 (DOUT), NP9.2 (DIN)
unnamed: NP9.4 (DOUT), NP10.2 (DIN)
unnamed: NP10.4 (DOUT), NP11.2 (DIN)
unnamed: NP11.4 (DOUT), NP12.2 (DIN)
unnamed: NP12.4 (DOUT), NP13.2 (DIN)
unnamed: NP13.4 (DOUT), NP14.2 (DIN)
unnamed: NP14.4 (DOUT), NP15.2 (DIN)
unnamed: NP15.4 (DOUT), NP16.2 (DIN)
unnamed: NP16.4 (DOUT), NP19.2 (DIN)
unnamed: NP17.2 (DIN), NP28.4 (DOUT)
unnamed: NP17.4 (DOUT), NP20.2 (DIN)
unnamed: NP18.2 (DIN), NP29.4 (DOUT)
unnamed: NP18.4 (DOUT), NP21.2 (DIN)
unnamed: NP19.4 (DOUT), NP22.2 (DIN)
unnamed: NP20.4 (DOUT), NP23.2 (DIN)
unnamed: NP21.4 (DOUT), NP24.2 (DIN)
unnamed: NP22.4 (DOUT), NP25.2 (DIN)
unnamed: NP23.4 (DOUT), NP26.2 (DIN)
unnamed: NP24.4 (DOUT), NP27.2 (DIN)
unnamed: NP25.4 (DOUT), NP28.2 (DIN)
unnamed: NP26.4 (DOUT), NP29.2 (DIN)
unnamed: R5.2, U3.47 (USB_DP)
unnamed: R6.2, U3.46 (USB_DM)

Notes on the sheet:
Crystal
Make sure R5 and R6 are close to RP2040
Make sure C44 is close to pin 44 of RP2040
Make sure C43 is close to pin 45 of RP2040
Flash
Power

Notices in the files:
KnGXT/firmware/macropaw.py:
SPDX-FileCopyrightText: 2022 Kodachi 6 14
SPDX-License-Identifier: GPL-3.0-or-later
Copyright 2022 Kodachi 6 14
modify it under the terms of the GNU General Public License as published
Beatboxer/hardware/KnH0F.kicad_pcb:
©2025 kodachi 6·14 llc
License: https://ohwr.org/cern_ohl_s_v2.txt
KnGXT.kicad_sch:
© 2022 kodachi 6•14, llc
KnGXT/hardware/KnGXT.kicad_sch:
© 2022 kodachi 6•14, llc // SPDX-License-Identifier: CERN-OHL-S-2.0
Open Source Hardware, CERN OHL 2.0: https://ohwr.org/cern_ohl_s_v2.txt
KnGYT/hardware/KnGYT.kicad_pcb:
©2023 kodachi 6·14 llc
